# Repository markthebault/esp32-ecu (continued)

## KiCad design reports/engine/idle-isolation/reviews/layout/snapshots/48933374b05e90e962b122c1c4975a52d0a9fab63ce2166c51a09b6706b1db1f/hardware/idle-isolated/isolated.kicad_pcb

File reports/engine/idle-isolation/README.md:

# Idle interface hardware evidence

This bundle covers the routed A5 carrier delta, isolated IAC-DRAFT2 accessory, UI/debug-guide update and conditional circuit experiments. **Physical outputs, fabrication and powered valve integration remain inhibited/on hold.** It adds no new closed-loop engine run; the earlier [33 engine runs and38 Speeduino checks](../idle-control/) remain separate evidence.

| Check | Result / boundary |
| --- | --- |
| A5 carrier | ERC0, DRC0, unconnected0, parity0. Original219refs/661pads/2973copper objects retained, except intended U3.13 net change;25 new copper objects |
| IAC-DRAFT2 | ERC0, DRC0, unconnected0, parity0.47refs/123 electrical pads, including unfitted copper star; all fitted electrical parts THT |
| Independent copper review | Initial bypass/shared-return defects corrected; sole logic/power return join at Q1 source; all15 broad power segments and31 local seeded segments retained |
| Nominal assembly projection | Eight back bodies have no front solder-pad overlap. C4 lead ends require trim/inspection before front DIP assembly. Exact3D/finished-hole/case fit unmeasured |
| Conditional circuit model | 25 ngspice45.2 runs,9 consequence checks, all complete. Eight independent controls and raw-data audit are in the circuit review |
| UI/configuration | 20 configuration/API tests,13 idle tests and9 Chrome workflow checks, including320/390/768/1440px layouts |
| Target builds | N16R8 web and A3 web build; ISR placement and USB ownership audits pass. Static checks do not measure hardware timing or runtime margins |

Use [validation-summary.json](validation-summary.json) for live-source/build bindings and [artifact-manifest.json](artifact-manifest.json) for every published artifact's bytes. Raw circuit decks, logs and full saved trace windows are in [circuit/](circuit/). Pulse traces retain1.9–2.2ms around their2ms command edge; the solver still integrates from zero. Other warm traces retain0–8ms; cold startup retains0–0.8s. `numdgt=17` preserves exported time ordering. Averages are time-weighted over declared windows. All25 exports have strictly increasing times.

The circuit is a separately authored lumped network with generic semiconductor and conditional opto/logic/supervisor/regulator behavior. It is not a vendor macromodel, parasitic extraction, valve-mechanics model or engine coupling. Cold startup applies DC carrier5V to an initially uncharged ideal100nF while the actuator source ramps. The sampled carrier inrush depends on ideal wiring/capacitance and timestep, and is **not a physical peak-current bound**. Late currents are reported separately. The deliberate ground bridge and drain-source short remain unsafe negative controls.

The gate can remain high briefly after an actuator return opens while the local rail discharges. A ground bridge can divert coil current into the carrier. The plot is a conditional model result, not a measured shutdown guarantee.

| Nominal top assembly | Mirrored back assembly |
| --- | --- |
|  |  |

These are native fabrication-layer illustrations, not manufacturing exports or a3D fit certificate. Plotting runs sequentially on writable cache copies because KiCad may write project settings. The source project bytes remain unchanged.

Independent records:

- [Architecture review](reviews/architecture/review.md) and its arithmetic/truth/DC-graph probe. Its preliminary RUN budget is superseded by the combined-loading finding below.
- [Initial copper findings](reviews/layout/initial-review.md), [final accessory review](reviews/layout/review.md), immutable snapshots and probes. Final raw results are in `reviews/layout/assembly-final/`.
- [A5 preservation/interface review](reviews/layout/a5/review.md), independent raw-S-expression audit and source-loading calculation.
- [Circuit review](reviews/circuit/review.md), independent controls, trace audit and exact source/artifact hashes.

Review scripts retain their original `.cache/engine/...` execution paths as provenance. For replay in a fresh checkout, restore each exported review tree to its named cache directory, point `snapshot-path.txt` files at the restored immutable bundle, then run its captured native-check runner/probe on writable cache copies. Preserve published evidence directories. Source PDFs, extracts and rendered datasheet pages remain local research inputs and are not redistributed. Pinned official KiCad footprint source copies retain the [KiCad library license/exception](https://www.kicad.org/libraries/license/); project-copy attribution is also in the hardware library notices.

**Release holds:** combined RUN/Q7/HCT source loading, loaded GPIO including R154, actual module/eFuse/JTAG geometry, exact PDIP driver guarantees/passive parts,1µs pulse/brownout behavior, independent protected actuator cutoff, actual valve R/L/current/decay, thermal, finished holes/lead trimming/back-part height, enclosure/RF/sealing. The [hardware guide](../../../docs/engine-idle-isolation.md) explains the implementation and reproduction. Nothing here establishes physical engine/vehicle, surge/EMI, thermal, splash or printed-fit qualification.

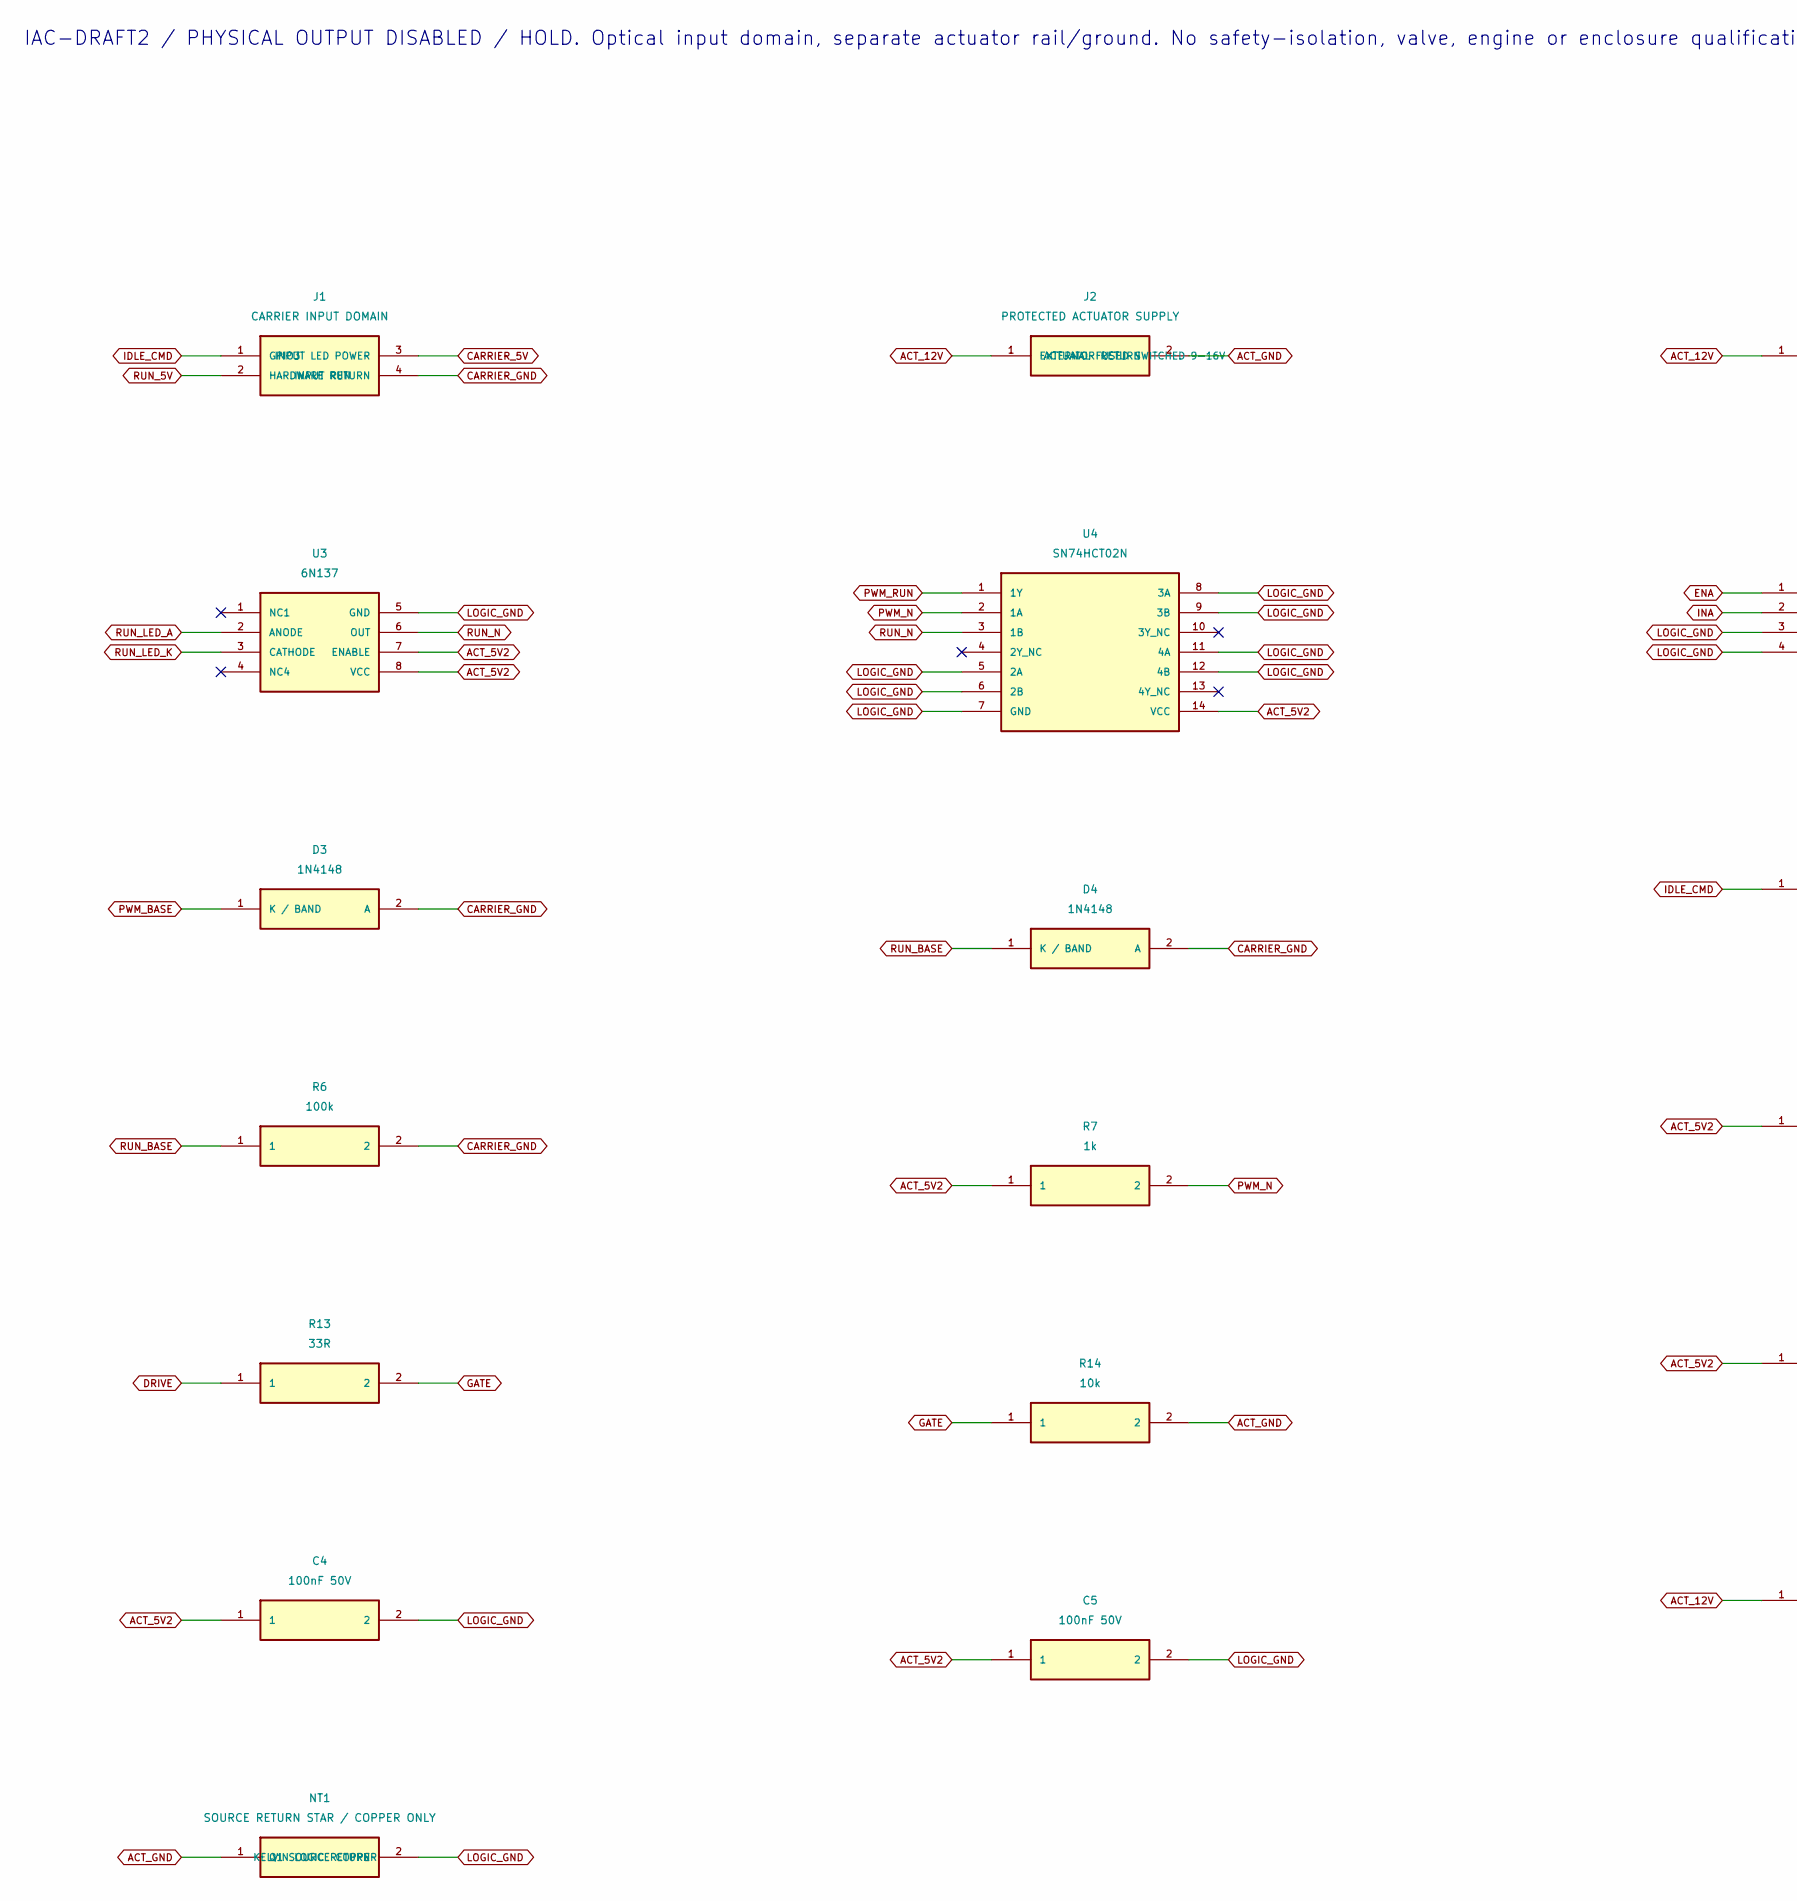
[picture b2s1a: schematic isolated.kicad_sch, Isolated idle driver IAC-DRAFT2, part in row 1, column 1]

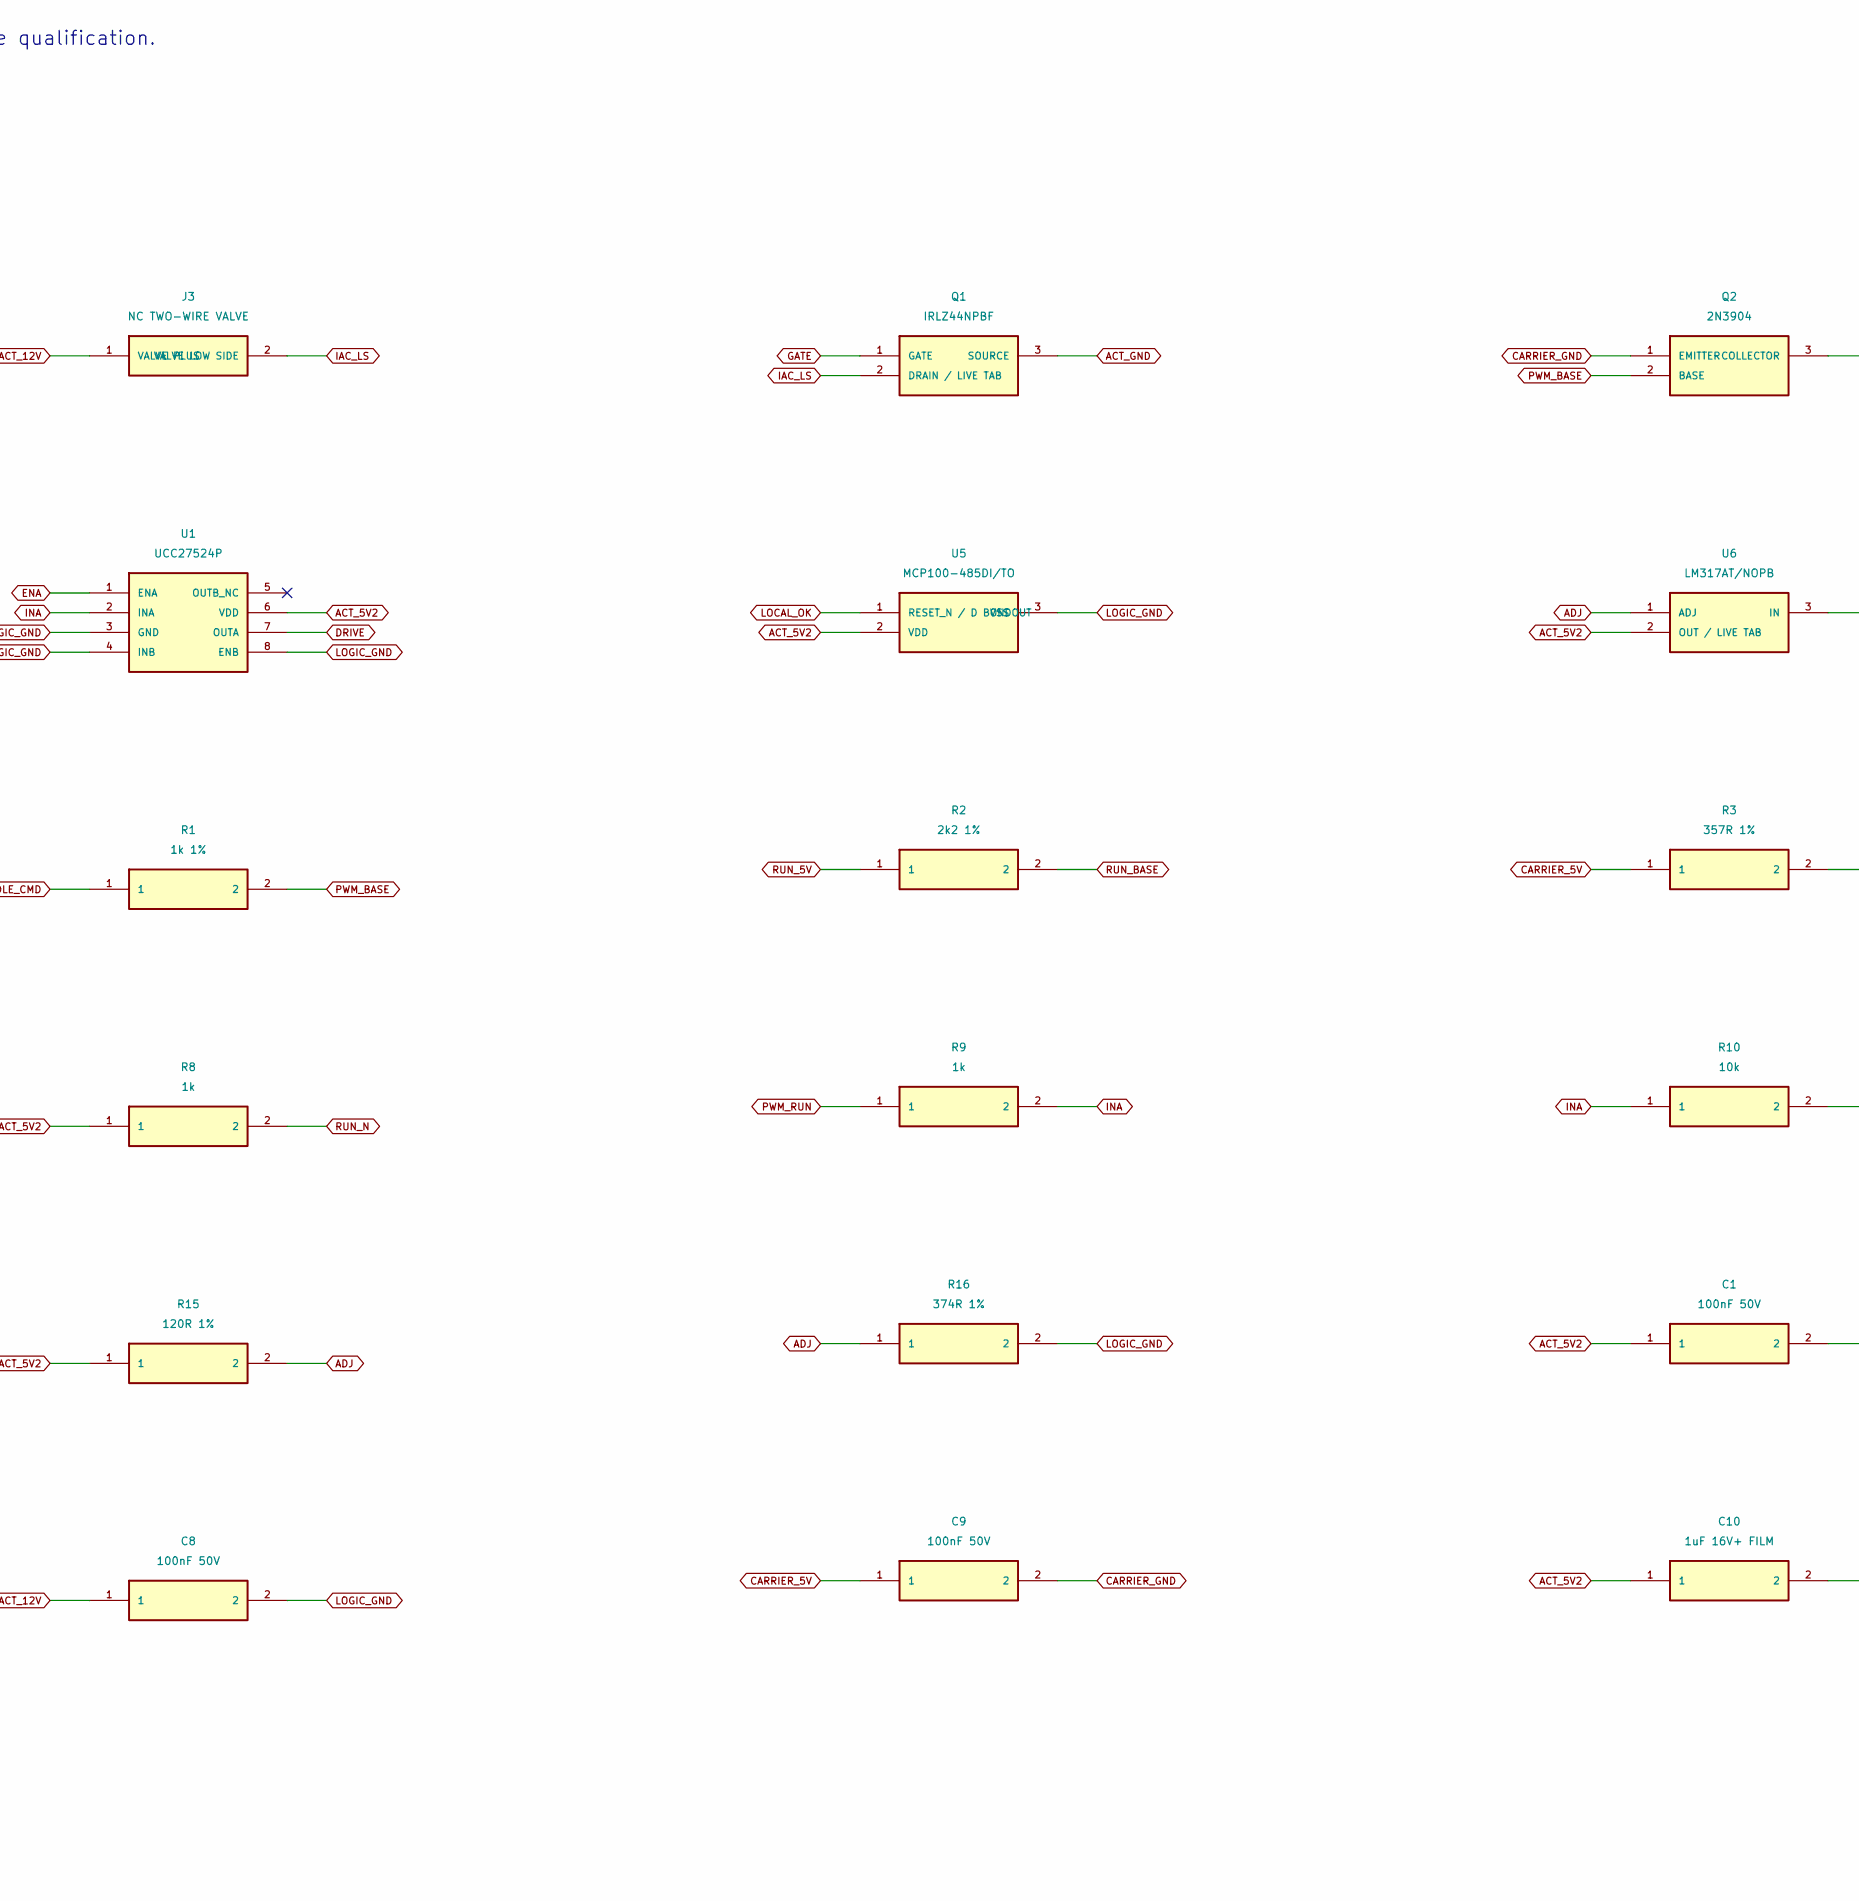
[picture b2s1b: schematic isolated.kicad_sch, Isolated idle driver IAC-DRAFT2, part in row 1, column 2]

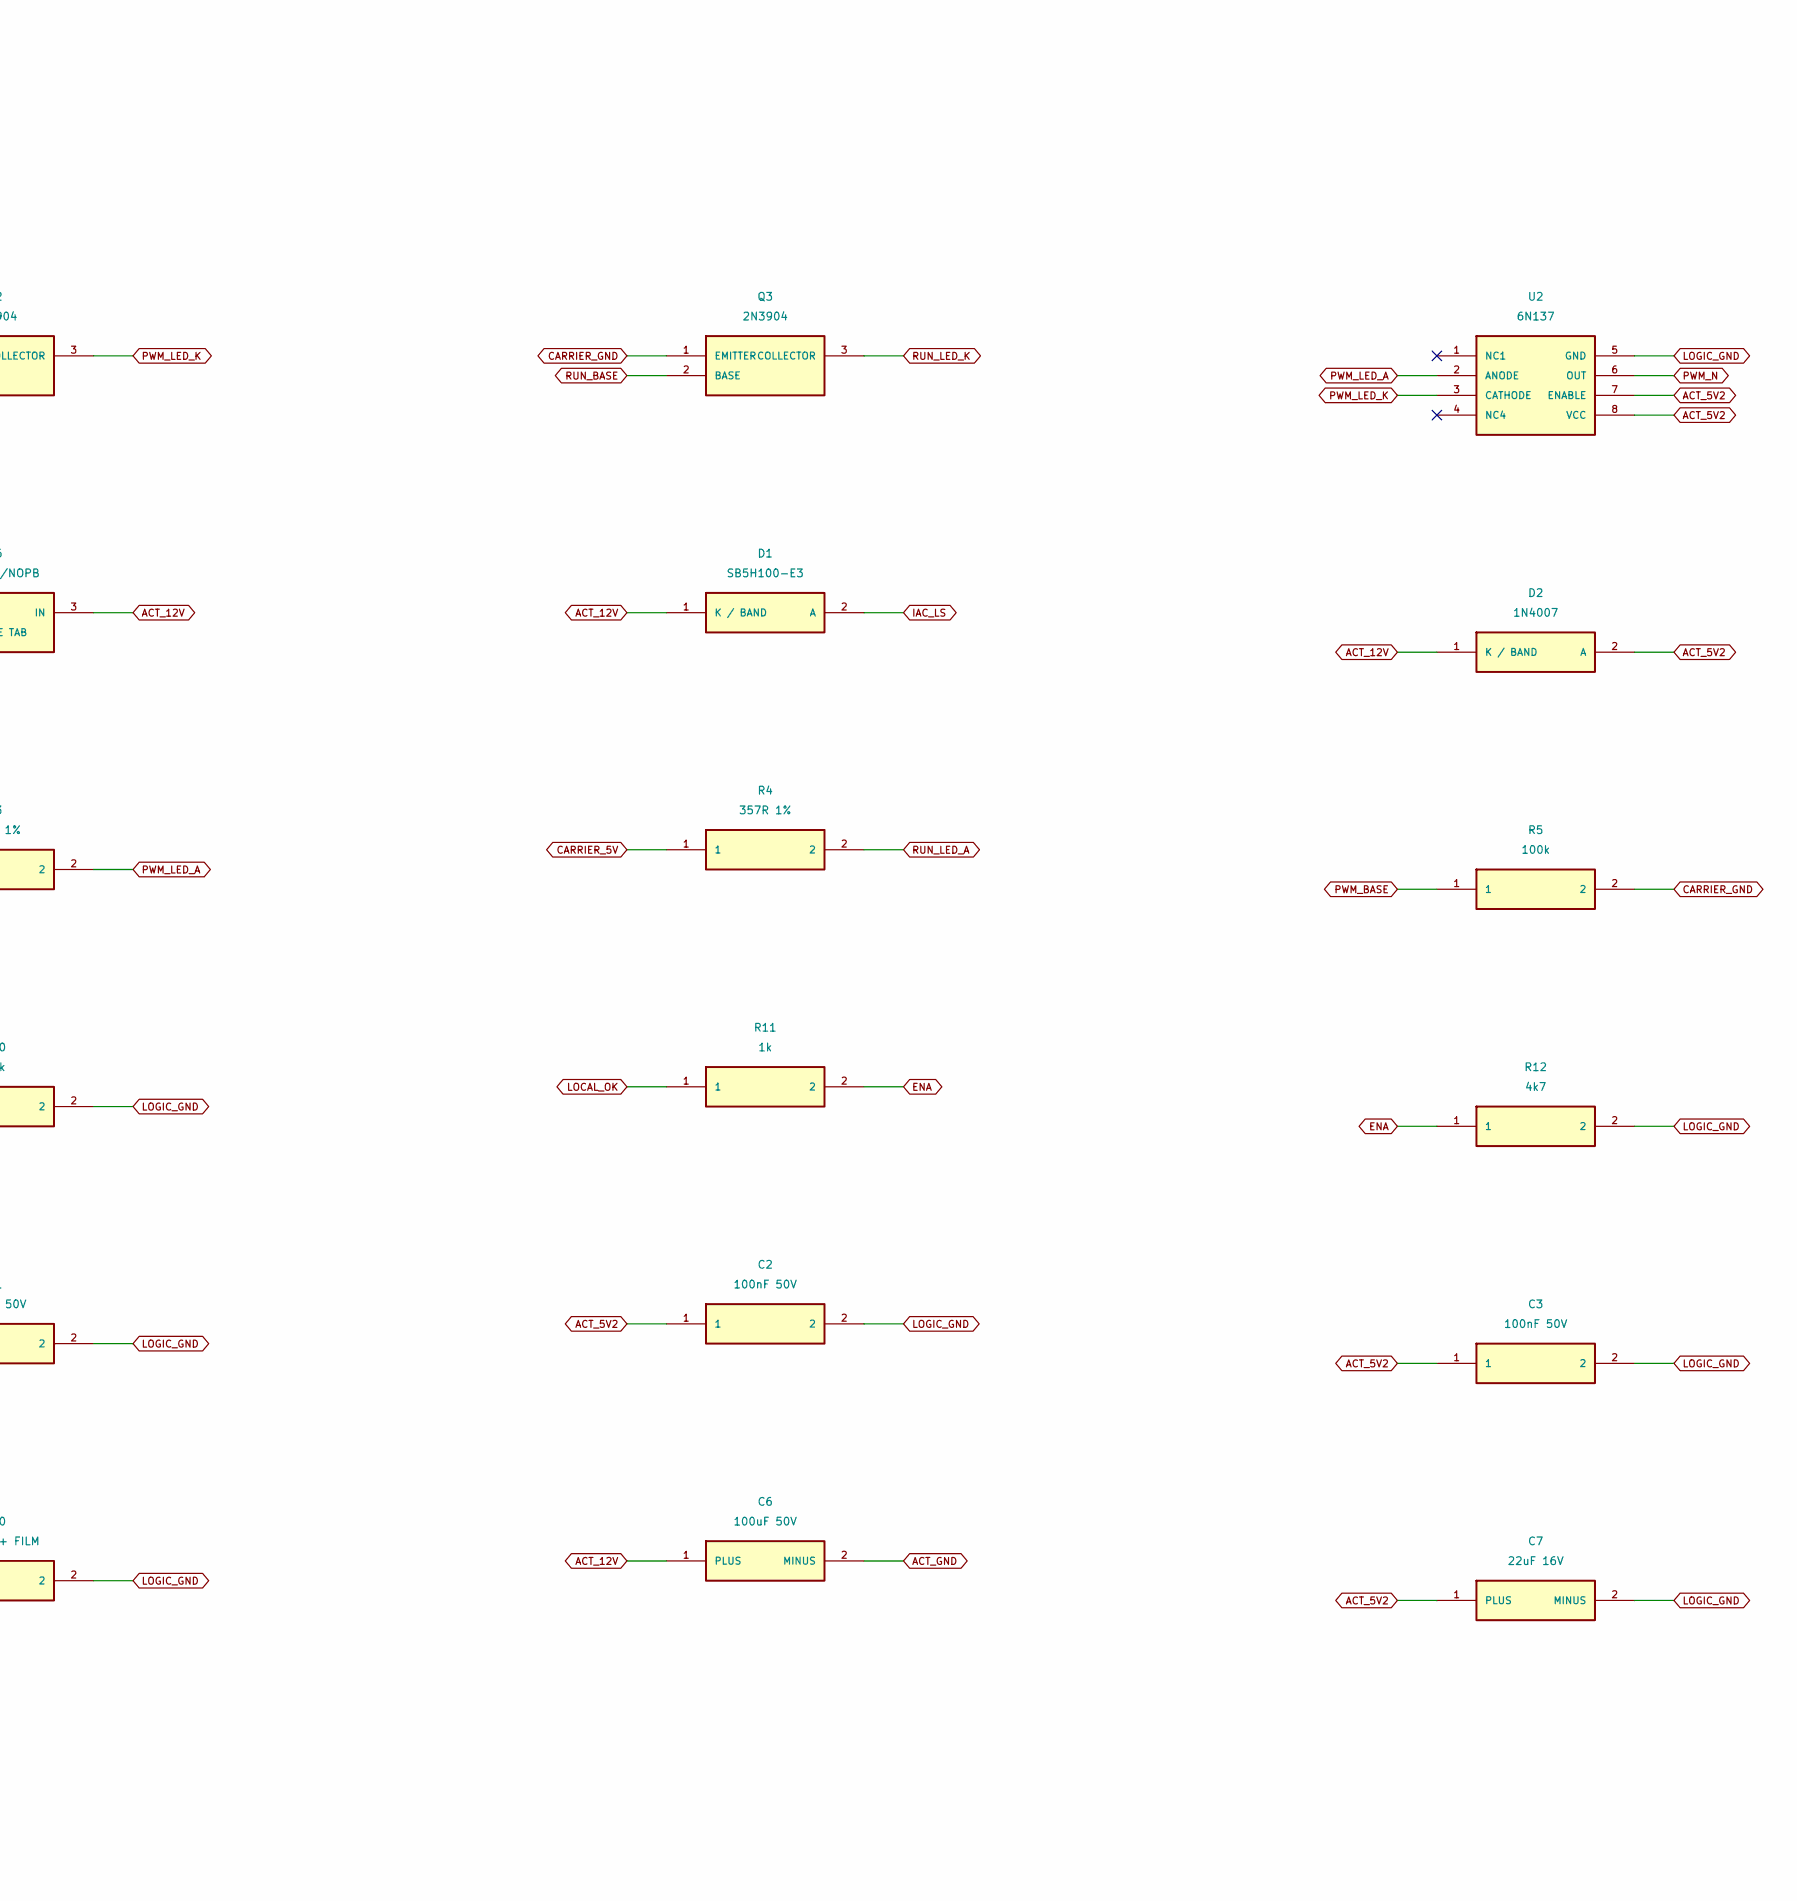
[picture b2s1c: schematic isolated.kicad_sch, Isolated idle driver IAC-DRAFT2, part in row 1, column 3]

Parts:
C1, C2, C3, C4, C5: 100nF 50V; C_Disc_D5.0mm_W2.5mm_P5.00mm_BackAssembly
C6: 100uF 50V; CP_Radial_D8.0mm_P3.50mm
C7: 22uF 16V; CP_Radial_D8.0mm_P3.50mm
C8, C9: 100nF 50V; C_Disc_D5.0mm_W2.5mm_P5.00mm
C10: 1uF 16V+ FILM; C_Rect_L7.2mm_W5.0mm_P5.00mm_BackAssembly
D1: SB5H100-E3; D_DO-201AD_P15.24mm_Horizontal; MPN SB5H100-E3/54
D2: 1N4007; D_DO-41_SOD81_P10.16mm_Horizontal; MPN 1N4007-E3/54
D3, D4: 1N4148; D_DO-35_SOD27_P3.81mm_Vertical_AnodeUp; MPN 1N4148-TAP
J1: CARRIER INPUT DOMAIN; JST_XH_B4B-XH-A_1x04_P2.50mm_Vertical; MPN B4B-XH-A(LF)(SN)
J2: PROTECTED ACTUATOR SUPPLY; TerminalBlock_Phoenix_MKDS-1,5-2-5.08_1x02_P5.08mm_Horizont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; MPN 1715721
J3: NC TWO-WIRE VALVE; JST_VH_B2P-VH_1x02_P3.96mm_Vertical; MPN B2P-VH(LF)(SN)
NT1: SOURCE RETURN STAR / COPPER ONLY; NetTie_Source_Star
Q1: IRLZ44NPBF; TO-220-3_Vertical; MPN IRLZ44NPBF
Q2, Q3: 2N3904; TO-92_Inline_Wide; MPN 2N3904BU
R1: 1k 1%; R_Axial_DIN0207_L6.3mm_D2.5mm_P2.54mm_Vertical
R2: 2k2 1%; R_Axial_DIN0207_L6.3mm_D2.5mm_P2.54mm_Vertical
R3, R4: 357R 1%; R_Axial_DIN0207_L6.3mm_D2.5mm_P2.54mm_Vertical
R5, R6: 100k; R_Axial_DIN0207_L6.3mm_D2.5mm_P2.54mm_Vertical
R7, R8, R9, R11: 1k; R_Axial_DIN0207_L6.3mm_D2.5mm_P2.54mm_Vertical
R10: 10k; R_Axial_DIN0207_L6.3mm_D2.5mm_P2.54mm_Vertical
R12: 4k7; R_Axial_DIN0207_L6.3mm_D2.5mm_P2.54mm_Vertical
R13: 33R; R_Axial_DIN0207_L6.3mm_D2.5mm_P2.54mm_Vertical_BackAssembly
R14: 10k; R_Axial_DIN0207_L6.3mm_D2.5mm_P2.54mm_Vertical_BackAssembly
R15: 120R 1%; R_Axial_DIN0207_L6.3mm_D2.5mm_P2.54mm_Vertical
R16: 374R 1%; R_Axial_DIN0207_L6.3mm_D2.5mm_P2.54mm_Vertical
U1: UCC27524P; DIP-8_W7.62mm_LongPads_BypassClearSilk; MPN UCC27524P.B
U2, U3: 6N137; DIP-8_W7.62mm_LongPads; MPN 6N137
U4: SN74HCT02N; DIP-14_W7.62mm_LongPads_BypassClearSilk; MPN SN74HCT02N
U5: MCP100-485DI/TO; TO-92_Inline_Wide; MPN MCP100-485DI/TO
U6: LM317AT/NOPB; TO-220-3_Vertical; MPN LM317AT/NOPB

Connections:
ACT_5V2: C1.1, C2.1, C3.1, C4.1, C5.1, C7.1 (PLUS), C10.1, D2.2 (A), R7.1, R8.1, R15.1, U1.6 (VDD), U2.7 (ENABLE), U2.8 (VCC), U3.7 (ENABLE), U3.8 (VCC), U4.14 (VCC), U5.2 (VDD), U6.2 (OUT / LIVE TAB)
ACT_12V: C6.1 (PLUS), C8.1, D1.1 (K / BAND), D2.1 (K / BAND), J2.1 (EXTERNAL FUSED SWITCHED 9-16V), J3.1 (VALVE PLUS), U6.3 (IN)
ACT_GND: C6.2 (MINUS), J2.2 (ACTUATOR RETURN), NT1.1 (Q1 SOURCE COPPER), Q1.3 (SOURCE), R14.2
ADJ: R15.2, R16.1, U6.1 (ADJ)
CARRIER_5V: C9.1, J1.3 (INPUT LED POWER), R3.1, R4.1
CARRIER_GND: C9.2, D3.2 (A), D4.2 (A), J1.4 (INPUT RETURN), Q2.1 (EMITTER), Q3.1 (EMITTER), R5.2, R6.2
DRIVE: R13.1, U1.7 (OUTA)
ENA: R11.2, R12.1, U1.1 (ENA)
GATE: Q1.1 (GATE), R13.2, R14.1
IAC_LS: D1.2 (A), J3.2 (VALVE LOW SIDE), Q1.2 (DRAIN / LIVE TAB)
IDLE_CMD: J1.1 (GPIO3), R1.1
INA: R9.2, R10.1, U1.2 (INA)
LOCAL_OK: R11.1, U5.1 (RESET_N / D BONDOUT)
LOGIC_GND: C1.2, C2.2, C3.2, C4.2, C5.2, C7.2 (MINUS), C8.2, C10.2, NT1.2 (KELVIN LOGIC RETURN), R10.2, R12.2, R16.2, U1.3 (GND), U1.4 (INB), U1.8 (ENB), U2.5 (GND), U3.5 (GND), U4.5 (2A), U4.6 (2B), U4.7 (GND), U4.8 (3A), U4.9 (3B), U4.11 (4A), U4.12 (4B), U5.3 (VSS)
PWM_BASE: D3.1 (K / BAND), Q2.2 (BASE), R1.2, R5.1
PWM_LED_A: R3.2, U2.2 (ANODE)
PWM_LED_K: Q2.3 (COLLECTOR), U2.3 (CATHODE)
PWM_N: R7.2, U2.6 (OUT), U4.2 (1A)
PWM_RUN: R9.1, U4.1 (1Y)
RUN_5V: J1.2 (HARDWARE RUN), R2.1
RUN_BASE: D4.1 (K / BAND), Q3.2 (BASE), R2.2, R6.1
RUN_LED_A: R4.2, U3.2 (ANODE)
RUN_LED_K: Q3.3 (COLLECTOR), U3.3 (CATHODE)
RUN_N: R8.2, U3.6 (OUT), U4.3 (1B)

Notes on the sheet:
IAC-DRAFT2 / PHYSICAL OUTPUT DISABLED / HOLD. Optical input domain, separate actuator rail/ground. No safety-isolation, valve, engine or enclosure qualification.

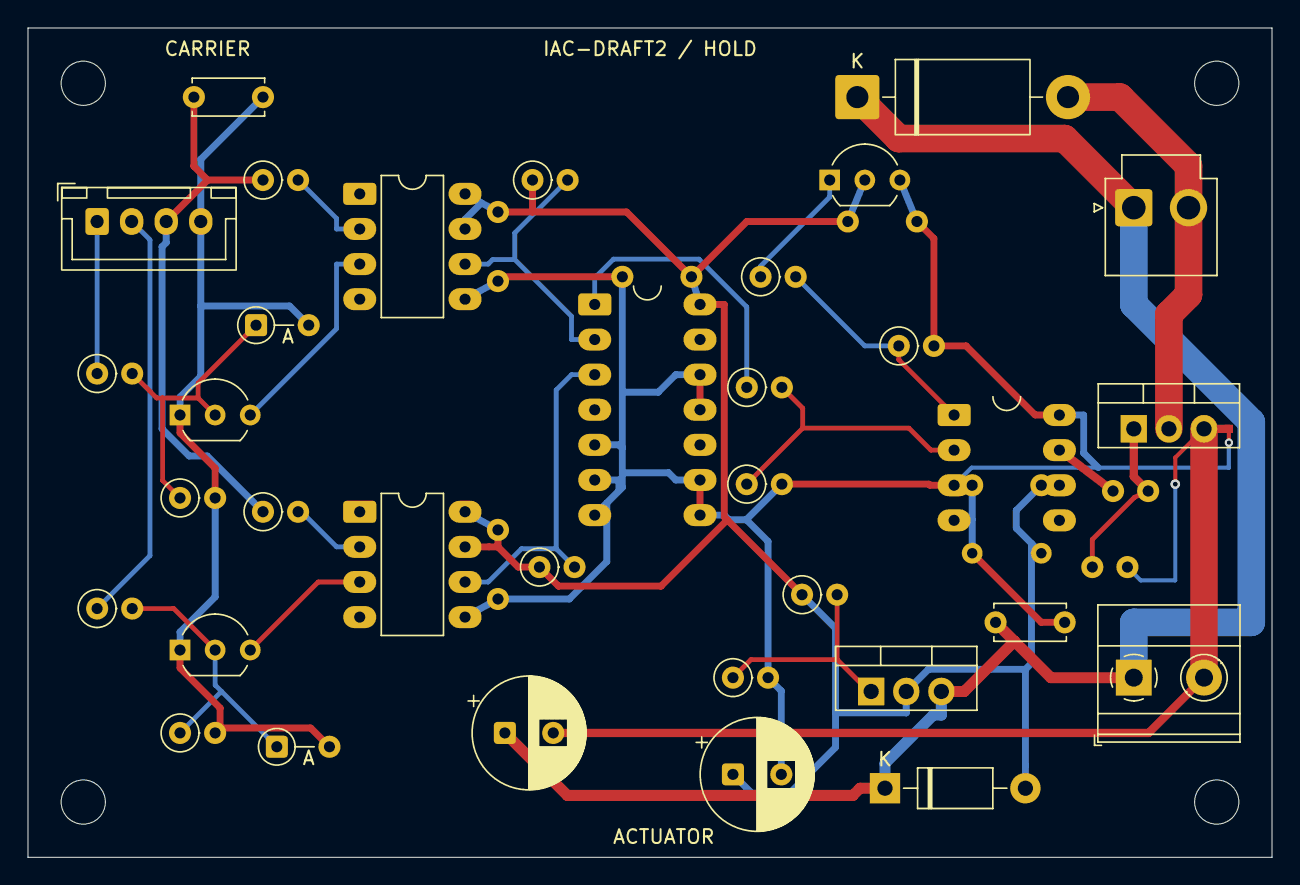
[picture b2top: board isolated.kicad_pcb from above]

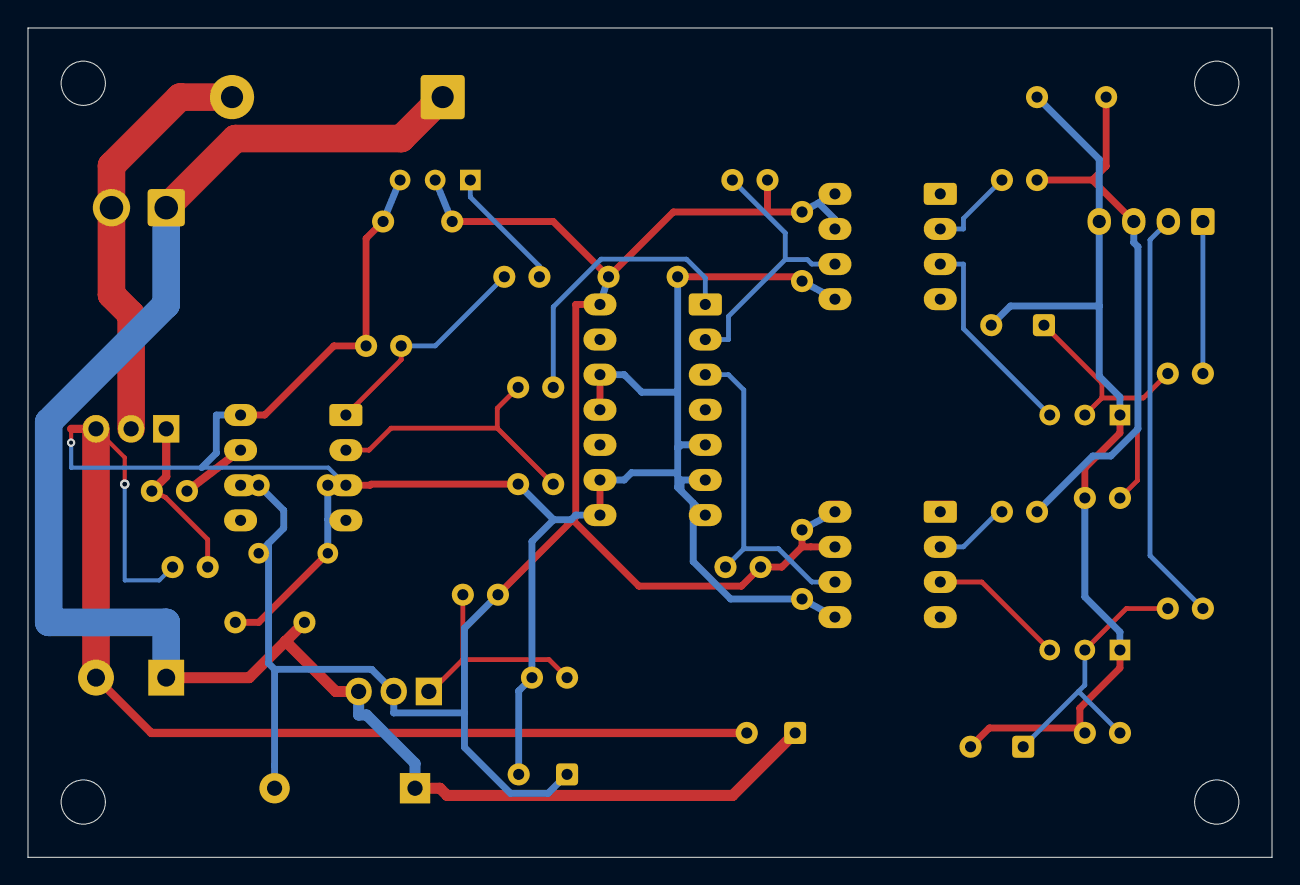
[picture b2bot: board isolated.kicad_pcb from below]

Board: 2 copper layers, 90.0 x 60.0 mm, 47 parts (8 on the bottom side), 24 nets.

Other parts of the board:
H1, H2, H3, H4: M3 ISOLATED MOUNT; MountingHole_3.2mm_M3
